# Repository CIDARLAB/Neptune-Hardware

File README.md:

Neptune is a complete, end-to-end microfluidic design suite for synthetic biologists. With Neptune, researchers and microfluidic designers have all the tools needed to design, fabricate, and control microfluidic devices. Neptune supports high level specification of a microfluidic chips layout and function. This high level specification includes a library of predefined microfluidic components commonly used in designs, including valves, gradient generators, serpentine mixers, and droplet generators. Neptune also provides a interface where researchers can control their microfluidic chip in real time. Fluid flow can be manipulated directly from the interface, making Neptune an ideal tool for running and controlling microfluidic chip experiments. Neptune also interfaces with and sources only low cost, open and readily available tools to fabricate and control microfluidic chips; Neptune provides a 3D printed control infrastructure for your chip, and fabrication itself leverages the MakerFluidics workflow to create the chip using a CNC mill.

# Neptune-Hardware

## Data Acquisition Board

## Syringe Pump

## Mounting Board

## uF Chip Holder

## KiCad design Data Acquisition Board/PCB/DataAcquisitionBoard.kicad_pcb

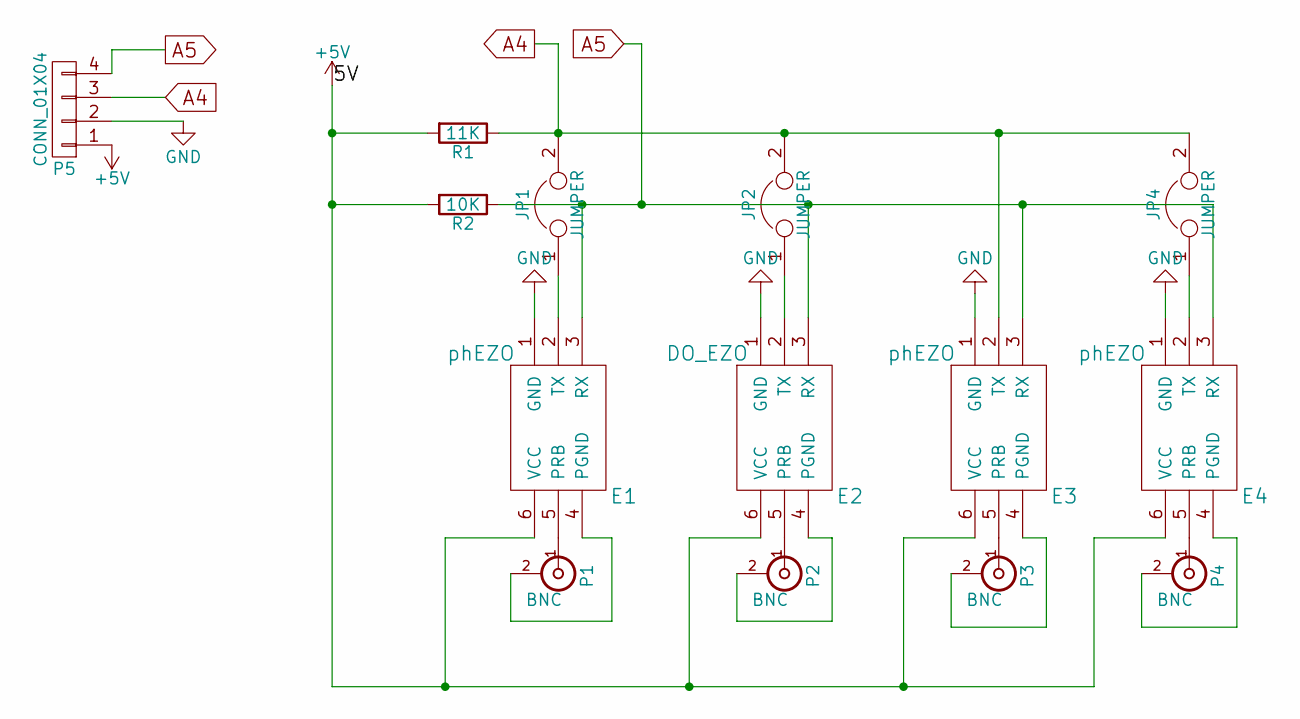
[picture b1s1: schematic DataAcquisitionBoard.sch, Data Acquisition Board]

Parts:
E1, E3, E4: phEZO
E2: DO_EZO; phEZO
JP1, JP2, JP4: JUMPER; Jumper_6.35mm
P1, P2, P3, P4: BNC; BNC_Socket_TYCO-AMP
P5: CONN_01X04; Pin_Header_Straight_1x04
R1: 11K; Resistor_Horizontal_RM7mm
R2: 10K; Resistor_Horizontal_RM7mm

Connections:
+5V: E1.6 (VCC), E2.6 (VCC), E3.6 (VCC), E4.6 (VCC), P5.1, R1.2, R2.2
A4: E3.2 (TX), JP1.2, JP2.2, JP4.2, P5.3, R1.1
A5: E1.3 (RX), E2.3 (RX), E3.3 (RX), E4.3 (RX), P5.4, R2.1
GND: E1.1 (GND), E2.1 (GND), E3.1 (GND), E4.1 (GND), P5.2
unnamed: E1.2 (TX), JP1.1
unnamed: E1.4 (PGND), P1.2 (Ext)
unnamed: E1.5 (PRB), P1.1 (In)
unnamed: E2.2 (TX), JP2.1
unnamed: E2.4 (PGND), P2.2 (Ext)
unnamed: E2.5 (PRB), P2.1 (In)
unnamed: E3.4 (PGND), P3.2 (Ext)
unnamed: E3.5 (PRB), P3.1 (In)
unnamed: E4.2 (TX), JP4.1
unnamed: E4.4 (PGND), P4.2 (Ext)
unnamed: E4.5 (PRB), P4.1 (In)

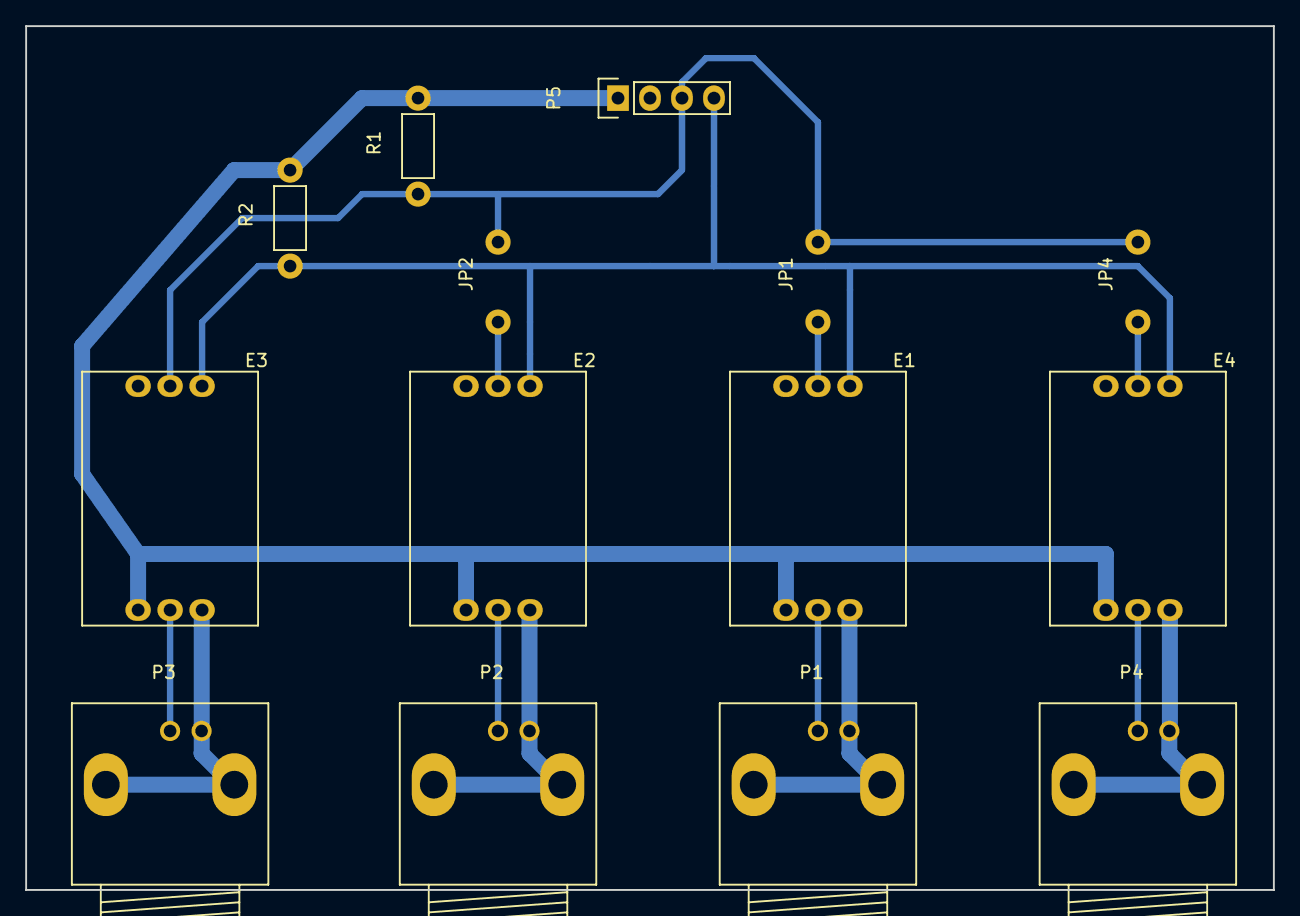
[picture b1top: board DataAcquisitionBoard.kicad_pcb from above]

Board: 2 copper layers, 99.1 x 68.6 mm, 14 parts (0 on the bottom side), 15 nets.

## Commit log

2016-06-06 Initial Commit
    Setup the repository directory structure and gitignore
2016-06-10 serial to hardware no shield
2016-06-13 Added the STL files, maybe this is the wrong directory for them so feel free to remove them..
    More importantly, I am adding a working example which recieves commands from the GUI and then spins the motors. This should all work well!
2016-06-20 Parametric Servo Arms
    Yayy, we can print out servo arms now. These are OpenSCAD files, and so
    far as I can see, you can choose:
    - The number of arms,
    - The length of the arms,
    - The size of the holes,
    - The gear size and shape
2016-06-23 4 servo set up
2016-06-29 Firmware_MASTER --> Parametric to any number of servos.
    This version of the firmware is parametric such that it will initiate
    any given number of servos through a initial synchronization signal from
    the GUI. NOTE: This code has errors and will not compile, I'll fix that
    soon. NOTE: This code does not account for the subtleties involved in
    having >12 servos. With >12 servo's, you will need to attach a servo
    shield, which will then involve using I2C communication. To be
2016-06-30 Merging my current work w/ restructured dev
2016-07-06 Zach's code; modifications made to connect 3 servos
2016-07-06 SHow and tell
    Zach's added to aid in show and tell; only works with Uno and up to the
    number of PWM pins on the arduino which is 6
2016-07-10 made an example that outputs PWM by Serial Comm
2016-07-14 Zach's code; PWM and angle conversions show and tell
2016-07-18 moved kestus' code to its own folder and added the master firmware
    Firmware_MASTER is the main working code and should be the final version
    going forward
2016-07-18 Made file structure more readable
2016-07-18 Becca use June 25 demo sketch!
2016-07-22 Edited small things
2016-08-01 Organized File structure
2016-08-03 New demo for doug, has all functionality of past plus more!
2016-08-03 Quick fixes
2016-08-23 Added JS for flow rate and changed around some files
2016-08-29 Added Software system initalization
    Edited other files as well
2016-08-29 Changed to JS file
2016-08-29 Added ability to go DOWN in flow rate code!
2016-08-30 Updated, took out console.logs
2016-09-15 Added smooth code for Becca
    System init
2016-09-23 Cleaning files
2016-09-23 Gcodes
2016-09-23 3D Printing initialization file
2016-09-23 Jamboree keychain
2016-09-23 Servo Arm
2016-09-23 Syringe holder
2016-09-23 Servo holder
2016-09-23 Pump mount
2016-10-06 Added OpenSCAD files
    Added past attempts to Ultimaker as well, but most importantly is the
    OpenSCAD files and the final folders for 1cc, 3cc, 10cc, and 60cc
    setups. These include piston arm, servo holder, syringe holder, and
    syringe attachment.
2016-10-06 Moved around files to organize folder
2016-10-07 Added new master
2016-10-09 BaseStrengthener
2016-10-12 Added uF holder
2016-10-17 Firmware Master is final firmware; does NOT init with software and has set analog and digital shield assignments
2016-10-17 Reorganized Firmware
2016-11-19 Reorganized Github repo
2016-11-19 Cleaned up fles
2016-11-22 Moved MEC Board and uF Chip Holder to separate Folders
2016-11-22 Reorganized all the Syringe Pump and Mounting board files
2016-11-22 Moved them out of the separate folder
2016-11-22 Upating some of the readmes and firmware location
2016-11-23 Added readme and lisence
2016-12-11 Completed PCB layout, added jumper footprint
2016-12-13 Finalized PCB layout
2016-12-15 Plotted Gerbers and drill file
2016-12-26 Code for Atlas Sensor Stamps v 0.01
2016-12-26 Single Reads and Continuous Reads working
2016-12-26 installing windows bye
2016-12-26 Moved DAQ Firmware into the respective Folder
2016-12-26 Moved all the PCB Files to the respective folder.
    Basically I'm just making sure the directories are in order here.
2017-01-22 Updated PCB to allow for chaining of multiple boards
2017-01-22 Modified PCB to allow for chaining of multiple boards
    Connect up to 4 PCBs
2017-01-31 Updated Gerber/Drill files
